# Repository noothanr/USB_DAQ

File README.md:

# USB_DAQ
USB based data aquisition module

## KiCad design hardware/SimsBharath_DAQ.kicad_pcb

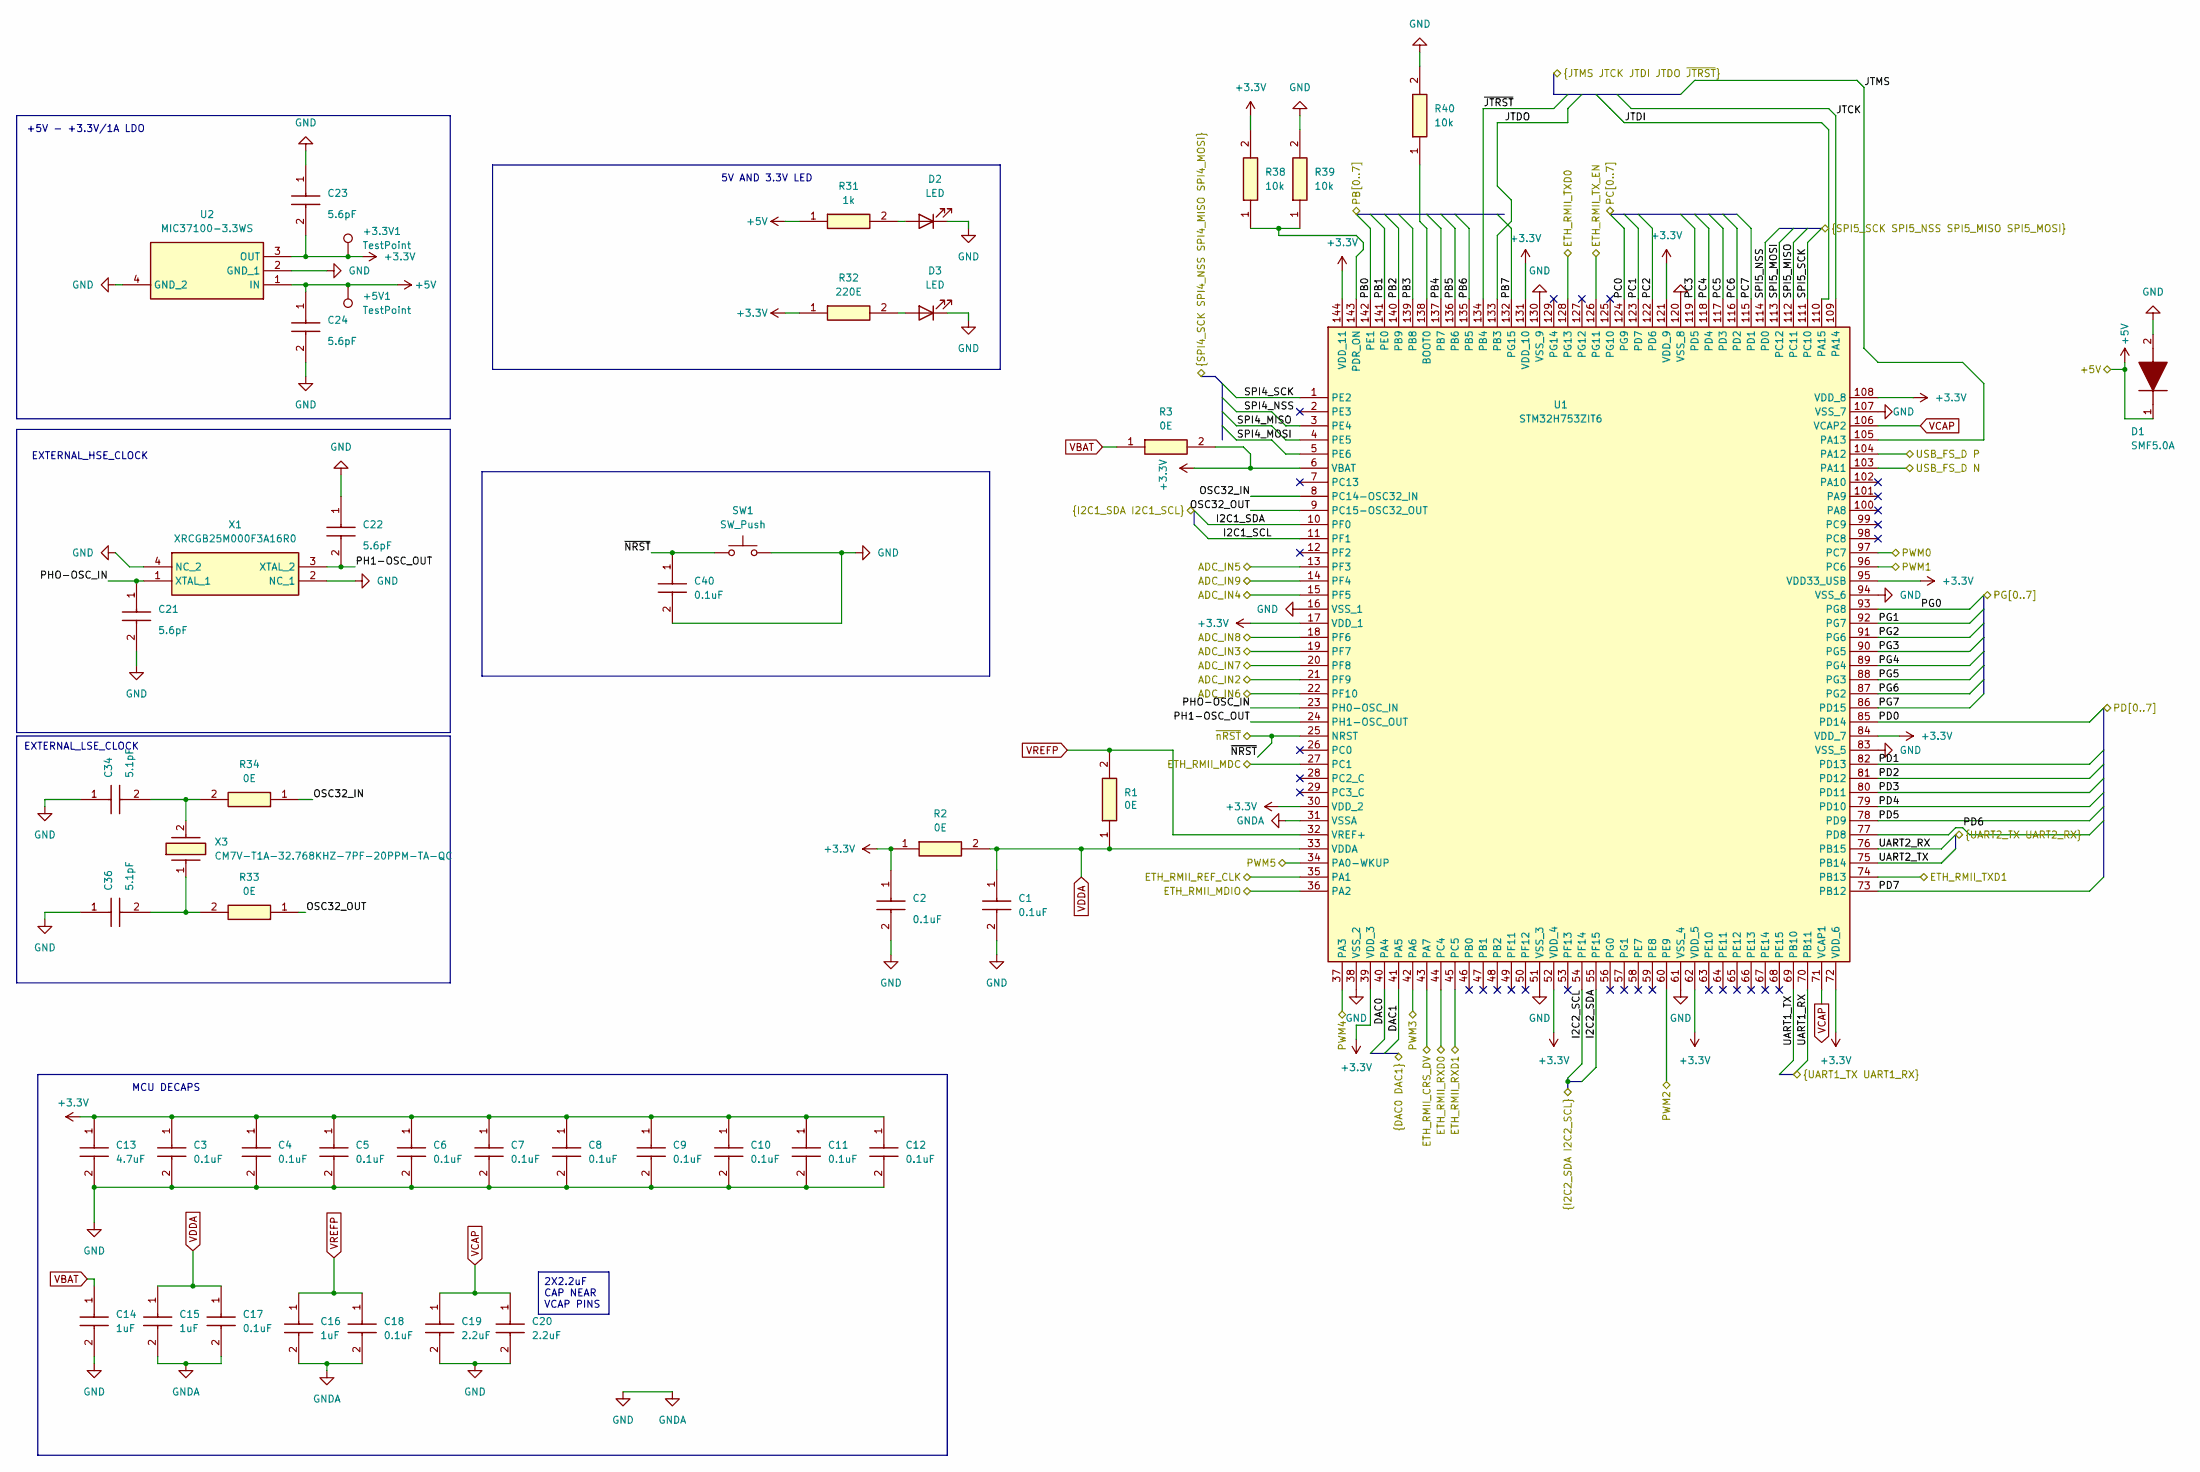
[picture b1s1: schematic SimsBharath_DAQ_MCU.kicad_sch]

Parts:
+3.3V1, +5V1: TestPoint; TestPoint_Pad_D1.5mm
C1, C2, C3, C4, C5, C6, C7, C8, C9, C10, C11, C12, C17, C18, C40: 0.1uF; GRM18x; Mouser Part Number 81-GRM188R72A104KA35
C13: 4.7uF; GRM18x; Mouser Part Number 81-GRM188R72A104KA35
C14, C15, C16: 1uF; GRM18x; Mouser Part Number 81-GRM188R72A104KA35
C19, C20: 2.2uF; GRM18x; Mouser Part Number 81-GRM188R72A104KA35
C21, C22, C23, C24: 5.6pF; GRM18x; Mouser Part Number 81-GRM188R72A104KA35
C34, C36: 5.1pF; GRM18x; Mouser Part Number 81-GRM188R72A104KA35
D1: SMF5.0A; SODFL3618X110N; Mouser Part Number 576-SMF5.0A
D2, D3: LED; LED_0603_1608Metric_Pad1.05x0.95mm_HandSolder
R1, R2, R3, R33, R34: 0E; RESC1608X95N; Mouser Part Number 81-PRF18BC471QB5RB
R31: 1k; RESC1608X95N; Mouser Part Number 81-PRF18BC471QB5RB
R32: 220E; RESC1608X95N; Mouser Part Number 81-PRF18BC471QB5RB
R38, R39, R40: 10k; RESC1608X95N; Mouser Part Number 81-PRF18BC471QB5RB
SW1: SW_Push; SW_PUSH_6mm_H4.3mm
U1: STM32H753ZIT6; QFP50P2200X2200X160-144N; Mouser Part Number 511-STM32H753ZIT6
U2: MIC37100-3.3WS; SOT230P700X180-4N; Mouser Part Number 998-MIC37100-3.3WS
X1: XRCGB25M000F3A16R0; XRCGB; Mouser Part Number 81-XRCGB25M000F3A16R
X3: CM7V-T1A-32.768KHZ-7PF-20PPM-TA-QC; CM7V32768TBQA020; Mouser Part Number 428-201345-MG01

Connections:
+5V: +5V1.1, C24.1, D1.1 (K), R31.1, U2.1 (IN); also elsewhere on the board
/CONNECTORS/ADC_IN2: U1.21 (PF9); also elsewhere on the board
/CONNECTORS/ADC_IN3: U1.19 (PF7); also elsewhere on the board
/CONNECTORS/ADC_IN4: U1.15 (PF5); also elsewhere on the board
/CONNECTORS/ADC_IN5: U1.13 (PF3); also elsewhere on the board
/CONNECTORS/ADC_IN6: U1.22 (PF10); also elsewhere on the board
/CONNECTORS/ADC_IN7: U1.20 (PF8); also elsewhere on the board
/CONNECTORS/ADC_IN8: U1.18 (PF6); also elsewhere on the board
/CONNECTORS/ADC_IN9: U1.14 (PF4); also elsewhere on the board
/CONNECTORS/DAC0: U1.40 (PA4); also elsewhere on the board
/CONNECTORS/DAC1: U1.41 (PA5); also elsewhere on the board
/CONNECTORS/ETH_RMII_CRS_DV: U1.43 (PA7); also elsewhere on the board
/CONNECTORS/ETH_RMII_MDC: U1.27 (PC1); also elsewhere on the board
/CONNECTORS/ETH_RMII_MDIO: U1.36 (PA2); also elsewhere on the board
/CONNECTORS/ETH_RMII_REF_CLK: U1.35 (PA1); also elsewhere on the board
/CONNECTORS/ETH_RMII_RXD0: U1.44 (PC4); also elsewhere on the board
/CONNECTORS/ETH_RMII_RXD1: U1.45 (PC5); also elsewhere on the board
/CONNECTORS/ETH_RMII_TXD0: U1.128 (PG13); also elsewhere on the board
/CONNECTORS/ETH_RMII_TXD1: U1.74 (PB13); also elsewhere on the board
/CONNECTORS/ETH_RMII_TX_EN: U1.126 (PG11); also elsewhere on the board
/CONNECTORS/I2C1_SCL: U1.11 (PF1); also elsewhere on the board
/CONNECTORS/I2C1_SDA: U1.10 (PF0); also elsewhere on the board
/CONNECTORS/I2C2_SCL: U1.54 (PF14); also elsewhere on the board
/CONNECTORS/I2C2_SDA: U1.55 (PF15); also elsewhere on the board
/CONNECTORS/JTCK: U1.109 (PA14); also elsewhere on the board
/CONNECTORS/JTDI: U1.110 (PA15); also elsewhere on the board
/CONNECTORS/JTDO: U1.133 (PB3); also elsewhere on the board
/CONNECTORS/JTMS: U1.105 (PA13); also elsewhere on the board
/CONNECTORS/PB0: U1.142 (PE1); also elsewhere on the board
/CONNECTORS/PB1: U1.141 (PE0); also elsewhere on the board
/CONNECTORS/PB2: U1.140 (PB9); also elsewhere on the board
/CONNECTORS/PB3: U1.139 (PB8); also elsewhere on the board
/CONNECTORS/PB4: U1.137 (PB7); also elsewhere on the board
/CONNECTORS/PB5: U1.136 (PB6); also elsewhere on the board
/CONNECTORS/PB6: U1.135 (PB5); also elsewhere on the board
/CONNECTORS/PB7: U1.132 (PG15); also elsewhere on the board
/CONNECTORS/PC0: U1.124 (PG9); also elsewhere on the board
/CONNECTORS/PC1: U1.123 (PD7); also elsewhere on the board
/CONNECTORS/PC2: U1.122 (PD6); also elsewhere on the board
/CONNECTORS/PC3: U1.119 (PD5); also elsewhere on the board
/CONNECTORS/PC4: U1.118 (PD4); also elsewhere on the board
/CONNECTORS/PC5: U1.117 (PD3); also elsewhere on the board
/CONNECTORS/PC6: U1.116 (PD2); also elsewhere on the board
/CONNECTORS/PC7: U1.115 (PD1); also elsewhere on the board
/CONNECTORS/PD0: U1.85 (PD14); also elsewhere on the board
/CONNECTORS/PD1: U1.82 (PD13); also elsewhere on the board
/CONNECTORS/PD2: U1.81 (PD12); also elsewhere on the board
/CONNECTORS/PD3: U1.80 (PD11); also elsewhere on the board
/CONNECTORS/PD4: U1.79 (PD10); also elsewhere on the board
/CONNECTORS/PD5: U1.78 (PD9); also elsewhere on the board
/CONNECTORS/PD6: U1.77 (PD8); also elsewhere on the board
/CONNECTORS/PD7: U1.73 (PB12); also elsewhere on the board
/CONNECTORS/PG0: U1.93 (PG8); also elsewhere on the board
/CONNECTORS/PG1: U1.92 (PG7); also elsewhere on the board
/CONNECTORS/PG2: U1.91 (PG6); also elsewhere on the board
/CONNECTORS/PG3: U1.90 (PG5); also elsewhere on the board
/CONNECTORS/PG4: U1.89 (PG4); also elsewhere on the board
/CONNECTORS/PG5: U1.88 (PG3); also elsewhere on the board
/CONNECTORS/PG6: U1.87 (PG2); also elsewhere on the board
/CONNECTORS/PG7: U1.86 (PD15); also elsewhere on the board
/CONNECTORS/PWM0: U1.97 (PC7); also elsewhere on the board
/CONNECTORS/PWM1: U1.96 (PC6); also elsewhere on the board
/CONNECTORS/PWM2: U1.60 (PE9); also elsewhere on the board
/CONNECTORS/PWM3: U1.42 (PA6); also elsewhere on the board
/CONNECTORS/PWM4: U1.37 (PA3); also elsewhere on the board
/CONNECTORS/PWM5: U1.34 (PA0-WKUP); also elsewhere on the board
/CONNECTORS/SPI4_MISO: U1.4 (PE5); also elsewhere on the board
/CONNECTORS/SPI4_MOSI: U1.5 (PE6); also elsewhere on the board
/CONNECTORS/SPI4_NSS: U1.3 (PE4); also elsewhere on the board
/CONNECTORS/SPI4_SCK: U1.1 (PE2); also elsewhere on the board
/CONNECTORS/SPI5_MISO: U1.112 (PC11); also elsewhere on the board
/CONNECTORS/SPI5_MOSI: U1.113 (PC12); also elsewhere on the board
/CONNECTORS/SPI5_NSS: U1.114 (PD0); also elsewhere on the board
/CONNECTORS/SPI5_SCK: U1.111 (PC10); also elsewhere on the board
/CONNECTORS/UART1_RX: U1.70 (PB11); also elsewhere on the board
/CONNECTORS/UART1_TX: U1.69 (PB10); also elsewhere on the board
/CONNECTORS/UART2_RX: U1.76 (PB15); also elsewhere on the board
/CONNECTORS/UART2_TX: U1.75 (PB14); also elsewhere on the board
/CONNECTORS/USB_FS_D N: U1.103 (PA11); also elsewhere on the board
/CONNECTORS/USB_FS_D P: U1.104 (PA12); also elsewhere on the board
/CONNECTORS/~JTRST: U1.134 (PB4); also elsewhere on the board
/MCU/OSC32_IN: R34.1, U1.8 (PC14-OSC32_IN)
/MCU/OSC32_OUT: R33.1, U1.9 (PC15-OSC32_OUT)
/MCU/PH1-OSC_OUT: C22.2, U1.24 (PH1-OSC_OUT), X1.3 (XTAL_2)
/MCU/PHO-OSC_IN: C21.1, U1.23 (PH0-OSC_IN), X1.1 (XTAL_1)
/MCU/~NRST: C40.1, SW1.1, U1.25 (NRST); also elsewhere on the board
GND: C1.2, C2.2, C3.2, C4.2, C5.2, C6.2, C7.2, C8.2, C9.2, C10.2, C11.2, C12.2, C13.2, C14.2, C15.2, C16.2, C17.2, C18.2, C19.2, C20.2, C21.2, C22.1, C23.1, C24.2, C34.1, C36.1, C40.2, D1.2 (A), D2.1 (K), D3.1 (K), R39.2, R40.2, SW1.2, U1.16 (VSS_1), U1.31 (VSSA), U1.38 (VSS_2), U1.51 (VSS_3), U1.61 (VSS_4), U1.83 (VSS_5), U1.94 (VSS_6), U1.107 (VSS_7), U1.120 (VSS_8), U1.130 (VSS_9), U2.2 (GND_1), U2.4 (GND_2), X1.2 (NC_1), X1.4 (NC_2); also elsewhere on the board
unnamed: C34.2, R34.2, X3.2
unnamed: C36.2, R33.2, X3.1
unnamed: D2.2 (A), R31.2
unnamed: D3.2 (A), R32.2
unnamed: R40.1, U1.138 (BOOT0)
unnamed: R38.1, R39.1, U1.143 (PDR_ON)
VCAP: C19.1, C20.1, U1.71 (VCAP1), U1.106 (VCAP2)
VDDA: C1.1, C15.1, C17.1, R1.1, R2.2, U1.33 (VDDA)
VREFP: C16.1, C18.1, R1.2, U1.32 (VREF+)

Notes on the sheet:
EXTERNAL_HSE_CLOCK
+5V - +3.3V/1A LDO
MCU DECAPS
5V AND 3.3V LED
EXTERNAL_LSE_CLOCK
2X2.2uF CAP NEAR VCAP PINS

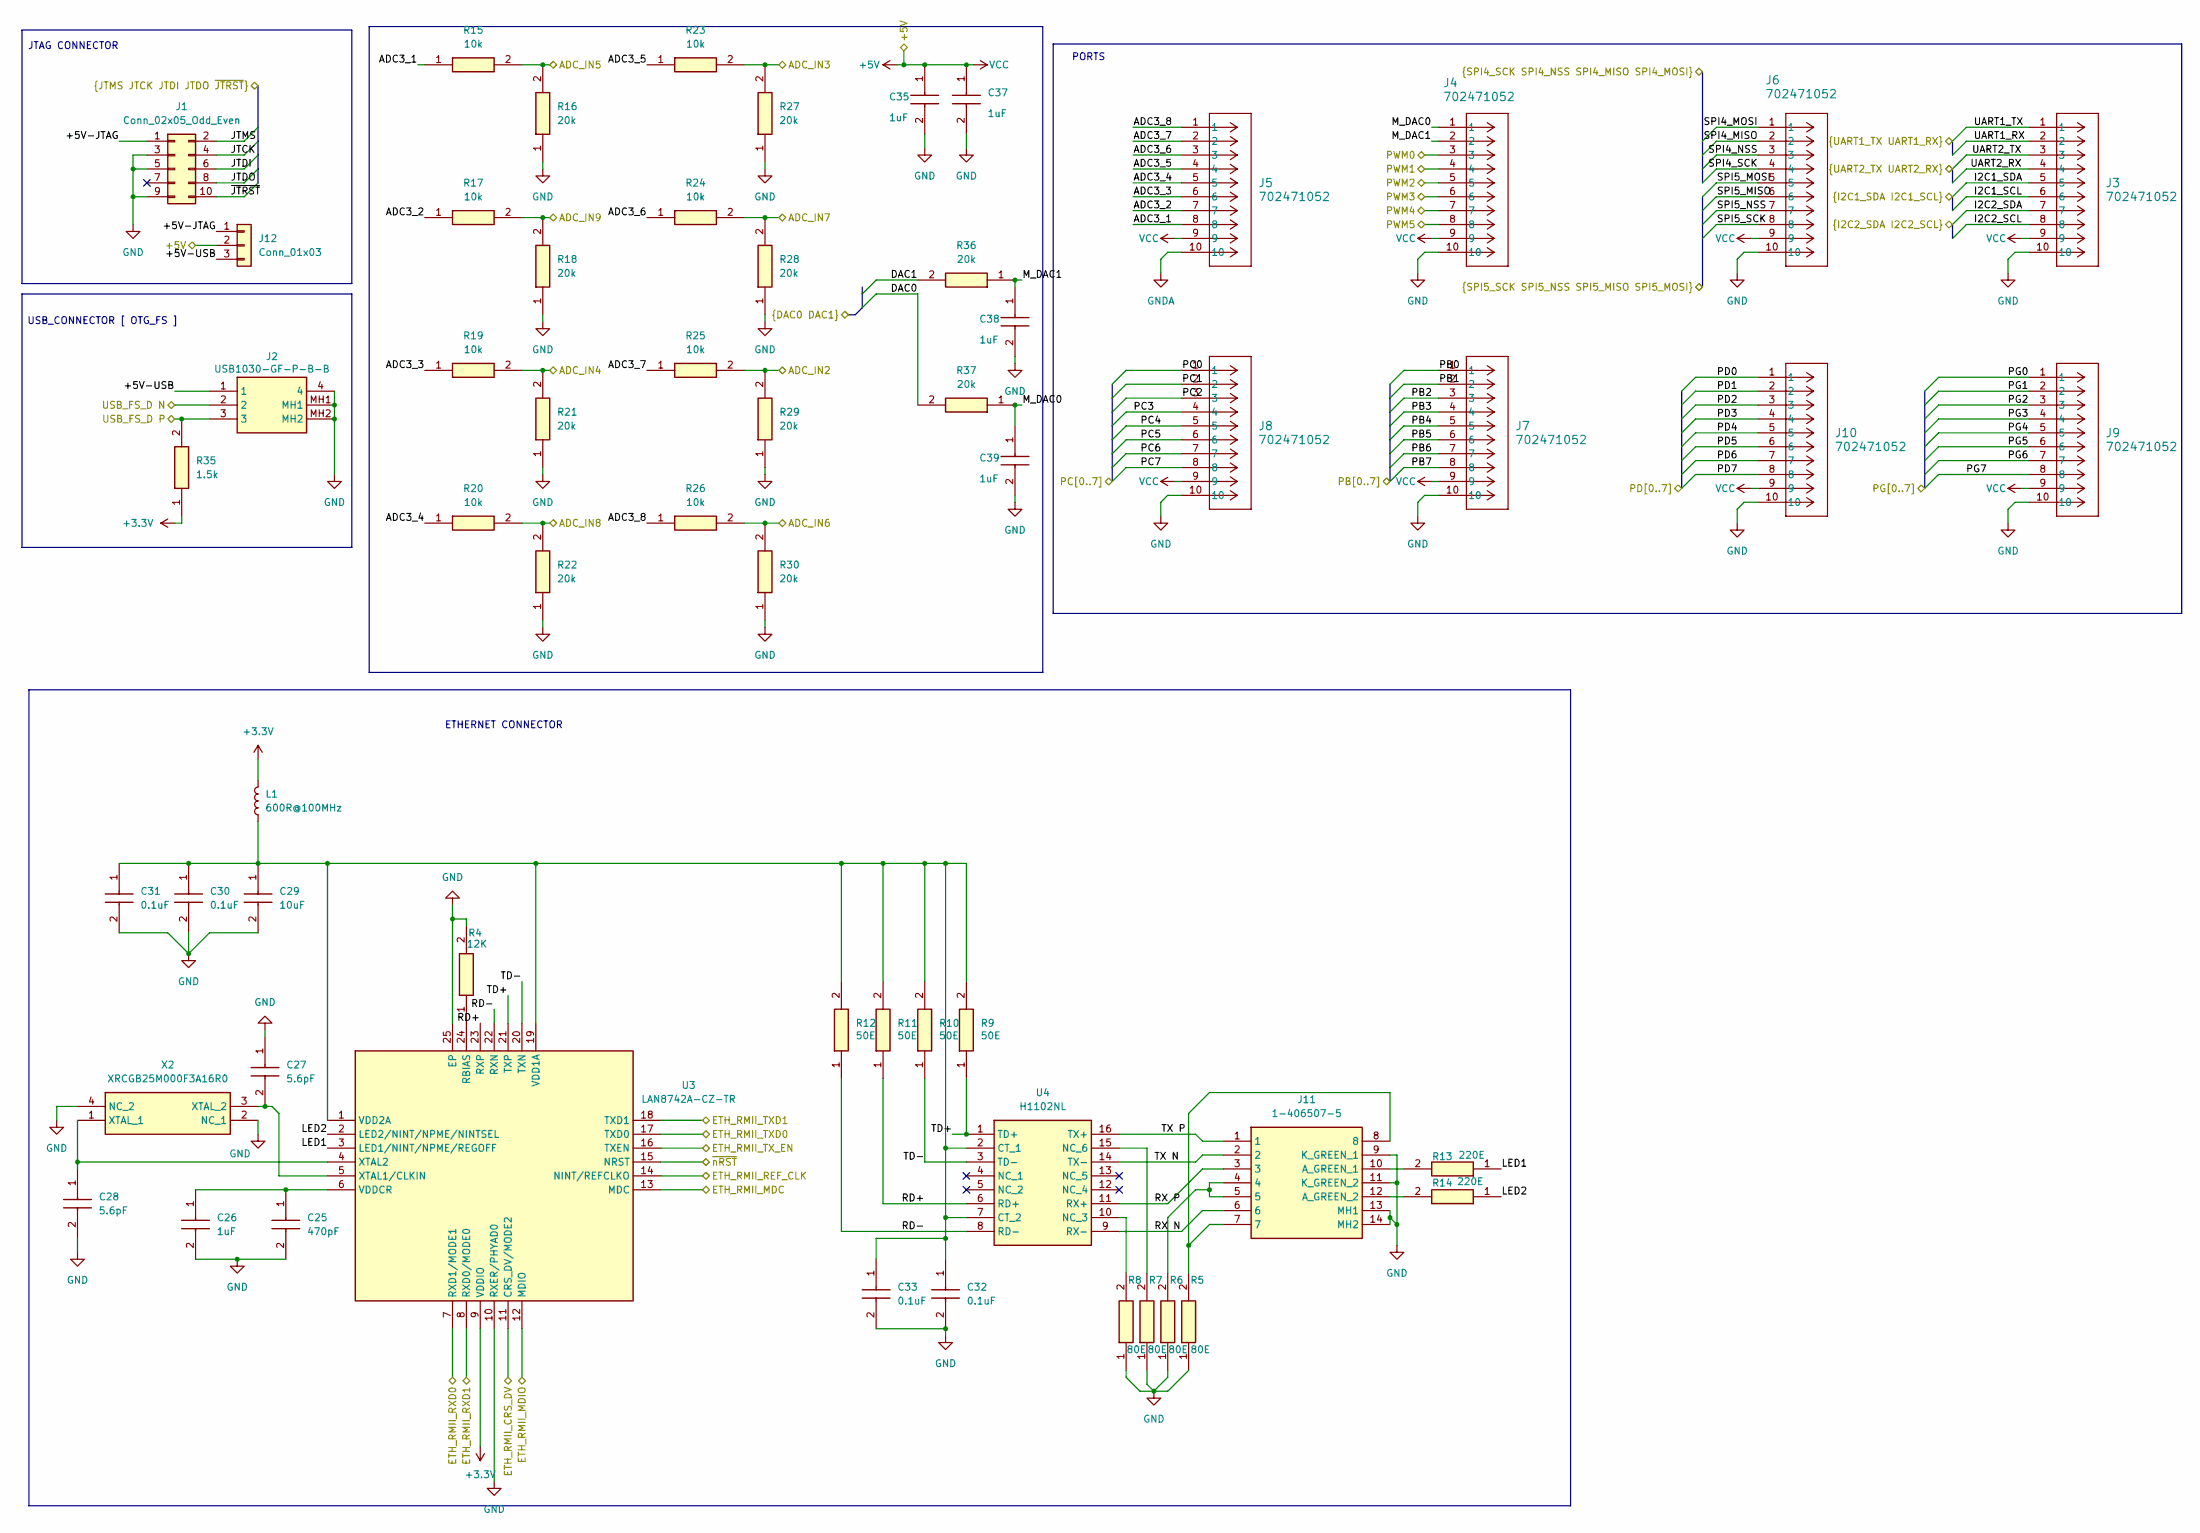
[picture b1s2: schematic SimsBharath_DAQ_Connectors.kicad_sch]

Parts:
C25: 470pF; GRM18x; Mouser Part Number 81-GRM188R72A104KA35
C26, C35, C37, C38, C39: 1uF; GRM18x; Mouser Part Number 81-GRM188R72A104KA35
C27, C28: 5.6pF; GRM18x; Mouser Part Number 81-GRM188R72A104KA35
C29: 10uF; GRM18x; Mouser Part Number 81-GRM188R72A104KA35
C30, C31, C32, C33: 0.1uF; GRM18x; Mouser Part Number 81-GRM188R72A104KA35
J1: Conn_02x05_Odd_Even; PinSocket_2x05_P2.00mm_Vertical
J2: USB1030-GF-P-B-B; USB1030GFPBB; Mouser Part Number 640-USB1030-GF-P-B-B
J3, J4, J5, J6, J7, J8, J9, J10: 702471052; CONN_7024710xx_MOL
J11: 1-406507-5; 14065075; Mouser Part Number 571-1-406507-5
J12: Conn_01x03; PinHeader_1x03_P2.54mm_Vertical
L1: 600R@100MHz; BLM18SP221SN1B
R4: 12K; RESC1608X95N; Mouser Part Number 81-PRF18BC471QB5RB
R5, R6, R7, R8: 80E; RESC1608X95N; Mouser Part Number 81-PRF18BC471QB5RB
R9, R10, R11, R12: 50E; RESC1608X95N; Mouser Part Number 81-PRF18BC471QB5RB
R13, R14: 220E; RESC1608X95N; Mouser Part Number 81-PRF18BC471QB5RB
R15, R17, R19, R20, R23, R24, R25, R26: 10k; RESC1608X95N; Mouser Part Number 81-PRF18BC471QB5RB
R16, R18, R21, R22, R27, R28, R29, R30, R36, R37: 20k; RESC1608X95N; Mouser Part Number 81-PRF18BC471QB5RB
R35: 1.5k; RESC1608X95N; Mouser Part Number 81-PRF18BC471QB5RB
U3: LAN8742A-CZ-TR; QFN50P400X400X100-25N-D; Mouser Part Number 579-LAN8742A-CZ-TR
U4: H1102NL; SOIC127P940X597-16N; Mouser Part Number 673-H1102NL
X2: XRCGB25M000F3A16R0; XRCGB; Mouser Part Number 81-XRCGB25M000F3A16R

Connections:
+5V: C35.1, C37.1, J3.9, J4.9, J5.9, J6.9, J7.9, J8.9, J9.9, J10.9, J12.2; also elsewhere on the board
/CONNECTORS/+5V-JTAG: J1.1, J12.1
/CONNECTORS/+5V-USB: J2.1, J12.3
/CONNECTORS/ADC3_1: J5.8, R15.1
/CONNECTORS/ADC3_2: J5.7, R17.1
/CONNECTORS/ADC3_3: J5.6, R19.1
/CONNECTORS/ADC3_4: J5.5, R20.1
/CONNECTORS/ADC3_5: J5.4, R23.1
/CONNECTORS/ADC3_6: J5.3, R24.1
/CONNECTORS/ADC3_7: J5.2, R25.1
/CONNECTORS/ADC3_8: J5.1, R26.1
/CONNECTORS/ADC_IN2: R25.2, R29.2; also elsewhere on the board
/CONNECTORS/ADC_IN3: R23.2, R27.2; also elsewhere on the board
/CONNECTORS/ADC_IN4: R19.2, R21.2; also elsewhere on the board
/CONNECTORS/ADC_IN5: R15.2, R16.2; also elsewhere on the board
/CONNECTORS/ADC_IN6: R26.2, R30.2; also elsewhere on the board
/CONNECTORS/ADC_IN7: R24.2, R28.2; also elsewhere on the board
/CONNECTORS/ADC_IN8: R20.2, R22.2; also elsewhere on the board
/CONNECTORS/ADC_IN9: R17.2, R18.2; also elsewhere on the board
/CONNECTORS/DAC0: R37.2; also elsewhere on the board
/CONNECTORS/DAC1: R36.2; also elsewhere on the board
/CONNECTORS/ETH_RMII_CRS_DV: U3.11 (CRS_DV/MODE2); also elsewhere on the board
/CONNECTORS/ETH_RMII_MDC: U3.13 (MDC); also elsewhere on the board
/CONNECTORS/ETH_RMII_MDIO: U3.12 (MDIO); also elsewhere on the board
/CONNECTORS/ETH_RMII_REF_CLK: U3.14 (NINT/REFCLKO); also elsewhere on the board
/CONNECTORS/ETH_RMII_RXD0: U3.7 (RXD1/MODE1); also elsewhere on the board
/CONNECTORS/ETH_RMII_RXD1: U3.8 (RXD0/MODE0); also elsewhere on the board
/CONNECTORS/ETH_RMII_TXD0: U3.17 (TXD0); also elsewhere on the board
/CONNECTORS/ETH_RMII_TXD1: U3.18 (TXD1); also elsewhere on the board
/CONNECTORS/ETH_RMII_TX_EN: U3.16 (TXEN); also elsewhere on the board
/CONNECTORS/I2C1_SCL: J3.6; also elsewhere on the board
/CONNECTORS/I2C1_SDA: J3.5; also elsewhere on the board
/CONNECTORS/I2C2_SCL: J3.8; also elsewhere on the board
/CONNECTORS/I2C2_SDA: J3.7; also elsewhere on the board
/CONNECTORS/JTCK: J1.4; also elsewhere on the board
/CONNECTORS/JTDI: J1.6; also elsewhere on the board
/CONNECTORS/JTDO: J1.8; also elsewhere on the board
/CONNECTORS/JTMS: J1.2; also elsewhere on the board
/CONNECTORS/LED1: R13.1, U3.3 (LED1/NINT/NPME/REGOFF)
/CONNECTORS/LED2: R14.1, U3.2 (LED2/NINT/NPME/NINTSEL)
/CONNECTORS/M_DAC0: C39.1, J4.1, R37.1
/CONNECTORS/M_DAC1: C38.1, J4.2, R36.1
/CONNECTORS/PB0: J7.1; also elsewhere on the board
/CONNECTORS/PB1: J7.2; also elsewhere on the board
/CONNECTORS/PB2: J7.3; also elsewhere on the board
/CONNECTORS/PB3: J7.4; also elsewhere on the board
/CONNECTORS/PB4: J7.5; also elsewhere on the board
/CONNECTORS/PB5: J7.6; also elsewhere on the board
/CONNECTORS/PB6: J7.7; also elsewhere on the board
/CONNECTORS/PB7: J7.8; also elsewhere on the board
/CONNECTORS/PC0: J8.1; also elsewhere on the board
/CONNECTORS/PC1: J8.2; also elsewhere on the board
/CONNECTORS/PC2: J8.3; also elsewhere on the board
/CONNECTORS/PC3: J8.4; also elsewhere on the board
/CONNECTORS/PC4: J8.5; also elsewhere on the board
/CONNECTORS/PC5: J8.6; also elsewhere on the board
/CONNECTORS/PC6: J8.7; also elsewhere on the board
/CONNECTORS/PC7: J8.8; also elsewhere on the board
/CONNECTORS/PD0: J10.1; also elsewhere on the board
/CONNECTORS/PD1: J10.2; also elsewhere on the board
/CONNECTORS/PD2: J10.3; also elsewhere on the board
/CONNECTORS/PD3: J10.4; also elsewhere on the board
/CONNECTORS/PD4: J10.5; also elsewhere on the board
/CONNECTORS/PD5: J10.6; also elsewhere on the board
/CONNECTORS/PD6: J10.7; also elsewhere on the board
/CONNECTORS/PD7: J10.8; also elsewhere on the board
/CONNECTORS/PG0: J9.1; also elsewhere on the board
/CONNECTORS/PG1: J9.2; also elsewhere on the board
/CONNECTORS/PG2: J9.3; also elsewhere on the board
/CONNECTORS/PG3: J9.4; also elsewhere on the board
/CONNECTORS/PG4: J9.5; also elsewhere on the board
/CONNECTORS/PG5: J9.6; also elsewhere on the board
/CONNECTORS/PG6: J9.7; also elsewhere on the board
/CONNECTORS/PG7: J9.8; also elsewhere on the board
/CONNECTORS/PWM0: J4.3; also elsewhere on the board
/CONNECTORS/PWM1: J4.4; also elsewhere on the board
/CONNECTORS/PWM2: J4.5; also elsewhere on the board
/CONNECTORS/PWM3: J4.6; also elsewhere on the board
/CONNECTORS/PWM4: J4.7; also elsewhere on the board
/CONNECTORS/PWM5: J4.8; also elsewhere on the board
/CONNECTORS/RD+: R11.1, U3.23 (RXP), U4.6 (RD+)
/CONNECTORS/RD-: R12.1, U3.22 (RXN), U4.8 (RD-)
/CONNECTORS/RX N: J11.6, U4.9 (RX-)
/CONNECTORS/RX P: J11.3, U4.11 (RX+)
/CONNECTORS/SPI4_MISO: J6.2; also elsewhere on the board
/CONNECTORS/SPI4_MOSI: J6.1; also elsewhere on the board
/CONNECTORS/SPI4_NSS: J6.3; also elsewhere on the board
/CONNECTORS/SPI4_SCK: J6.4; also elsewhere on the board
/CONNECTORS/SPI5_MISO: J6.6; also elsewhere on the board
/CONNECTORS/SPI5_MOSI: J6.5; also elsewhere on the board
/CONNECTORS/SPI5_NSS: J6.7; also elsewhere on the board
/CONNECTORS/SPI5_SCK: J6.8; also elsewhere on the board
/CONNECTORS/TD+: R9.1, U3.21 (TXP), U4.1 (TD+)
/CONNECTORS/TD-: R10.1, U3.20 (TXN), U4.3 (TD-)
/CONNECTORS/TX N: J11.2, U4.14 (TX-)
/CONNECTORS/TX P: J11.1, U4.16 (TX+)
/CONNECTORS/UART1_RX: J3.2; also elsewhere on the board
/CONNECTORS/UART1_TX: J3.1; also elsewhere on the board
/CONNECTORS/UART2_RX: J3.4; also elsewhere on the board
/CONNECTORS/UART2_TX: J3.3; also elsewhere on the board
/CONNECTORS/USB_FS_D N: J2.2; also elsewhere on the board
/CONNECTORS/USB_FS_D P: J2.3, R35.2; also elsewhere on the board
/CONNECTORS/~JTRST: J1.10; also elsewhere on the board
/MCU/~NRST: U3.15 (NRST); also elsewhere on the board
GND: C25.2, C26.2, C27.1, C28.2, C29.2, C30.2, C31.2, C32.2, C33.2, C35.2, C37.2, C38.2, C39.2, J1.3, J1.5, J1.9, J2.4, J2.MH1, J2.MH2, J3.10, J4.10, J5.10, J6.10, J7.10, J8.10, J9.10, J10.10, J11.9 (K_GREEN_1), J11.11 (K_GREEN_2), J11.13 (MH1), J11.14 (MH2), R4.2, R5.1, R6.1, R7.1, R8.1, R16.1, R18.1, R21.1, R22.1, R27.1, R28.1, R29.1, R30.1, U3.10 (RXER/PHYAD0), U3.25 (EP), X2.2 (NC_1), X2.4 (NC_2); also elsewhere on the board
unnamed: J11.10 (A_GREEN_1), R13.2
unnamed: J11.12 (A_GREEN_2), R14.2
unnamed: J11.4, J11.5, R6.2
unnamed: J11.7, J11.8, R5.2
unnamed: R4.1, U3.24 (RBIAS)
unnamed: C29.1, C30.1, C31.1, C32.1, C33.1, L1.1, R9.2, R10.2, R11.2, R12.2, U3.1 (VDD2A), U3.19 (VDD1A), U4.2 (CT_1), U4.7 (CT_2)
unnamed: C25.1, C26.1, U3.6 (VDDCR)
unnamed: C27.2, U3.5 (XTAL1/CLKIN), X2.3 (XTAL_2)
unnamed: C28.1, U3.4 (XTAL2), X2.1 (XTAL_1)
unnamed: R8.2, U4.10 (NC_3)
unnamed: R7.2, U4.15 (NC_6)

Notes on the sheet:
JTAG CONNECTOR
USB_CONNECTOR [ OTG_FS ]
ETHERNET CONNECTOR
PORTS

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
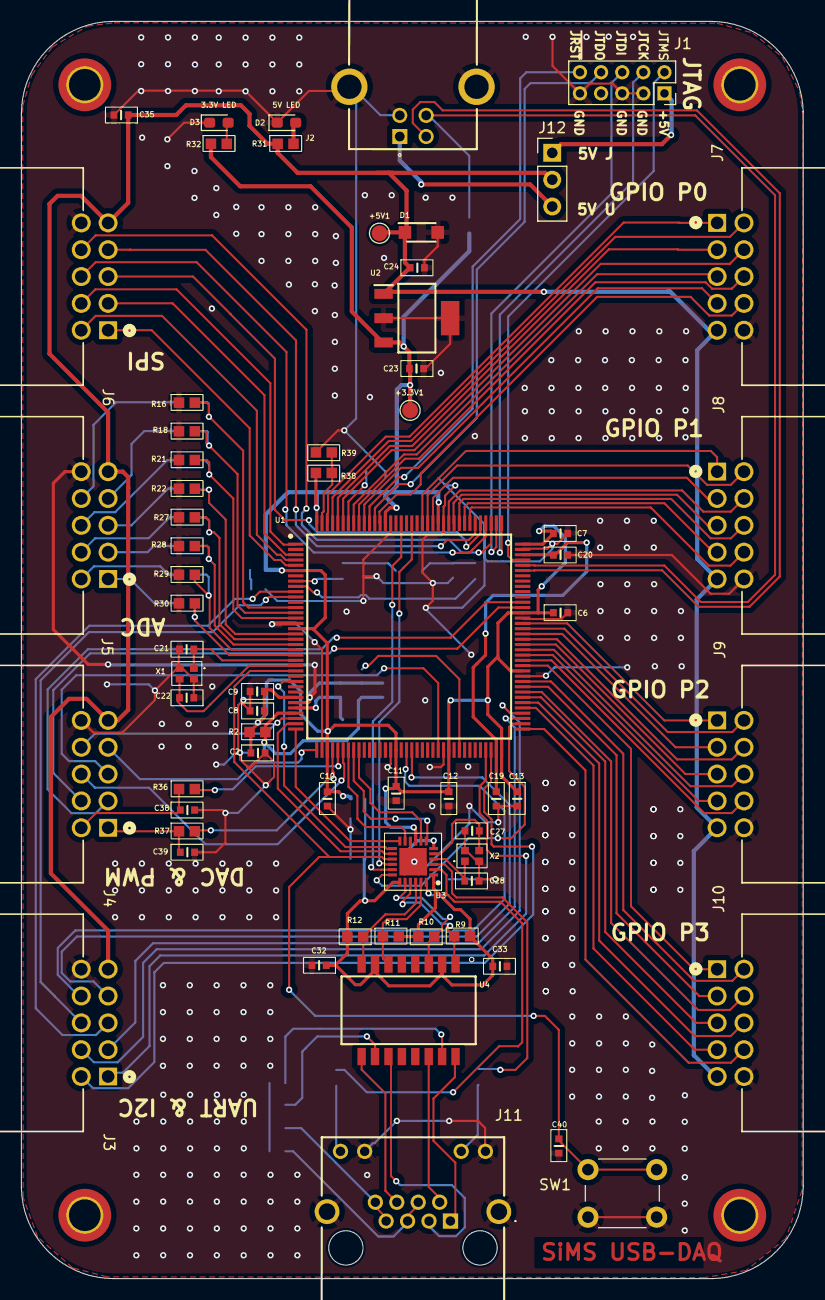
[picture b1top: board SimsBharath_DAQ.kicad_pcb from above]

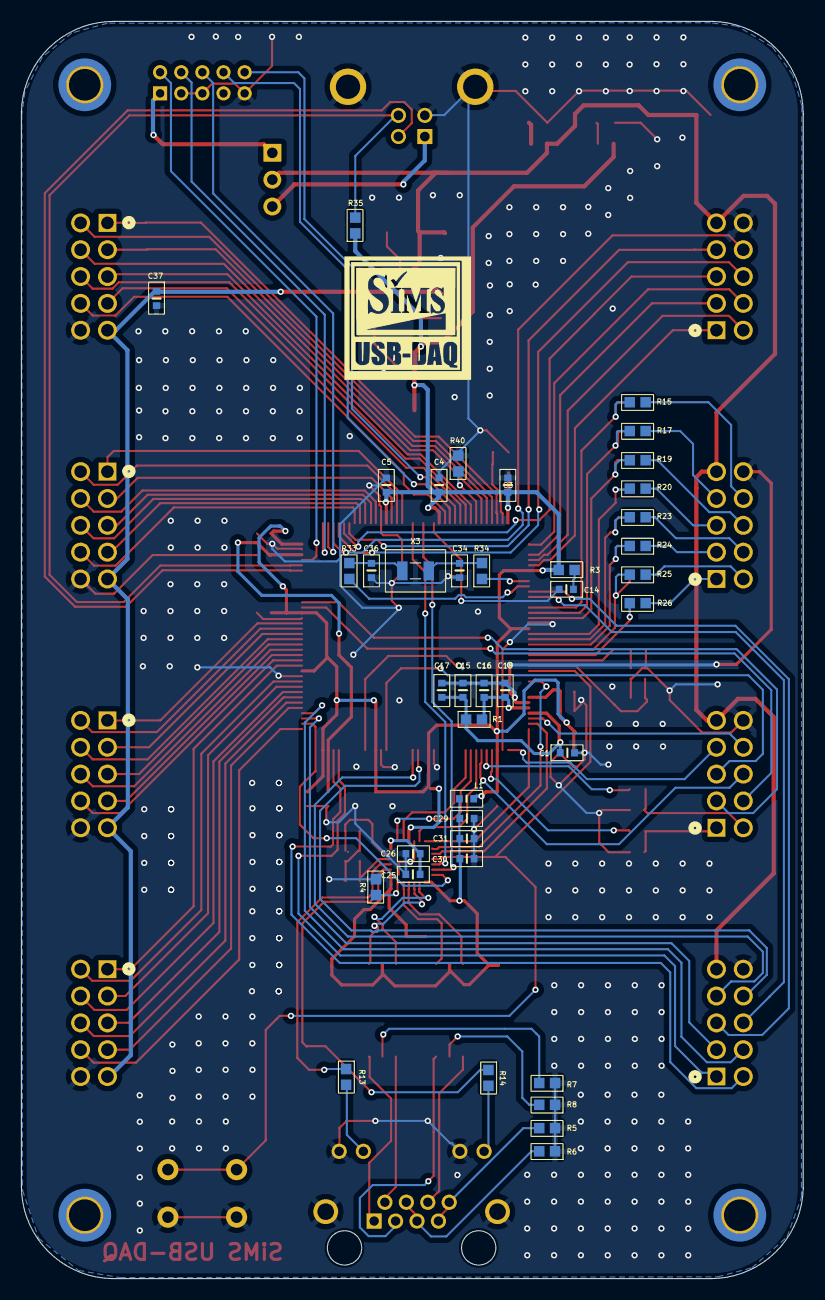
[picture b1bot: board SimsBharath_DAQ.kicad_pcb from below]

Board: 2 copper layers, 74.0 x 119.0 mm, 106 parts (40 on the bottom side), 131 nets.

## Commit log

2025-12-16 added hardware folder
2025-12-16 added the
2025-12-19 Add hardware folder and project files
2025-12-19 In layout finalised Board Dimensions ...
2025-12-20 completed the design
2025-12-22 completed the design with perfect mechanics
2025-12-22 changed header spacing
2025-12-23 Final Updated design
2025-12-24 final submission
2025-12-24 The other design files
2025-12-24 final update
